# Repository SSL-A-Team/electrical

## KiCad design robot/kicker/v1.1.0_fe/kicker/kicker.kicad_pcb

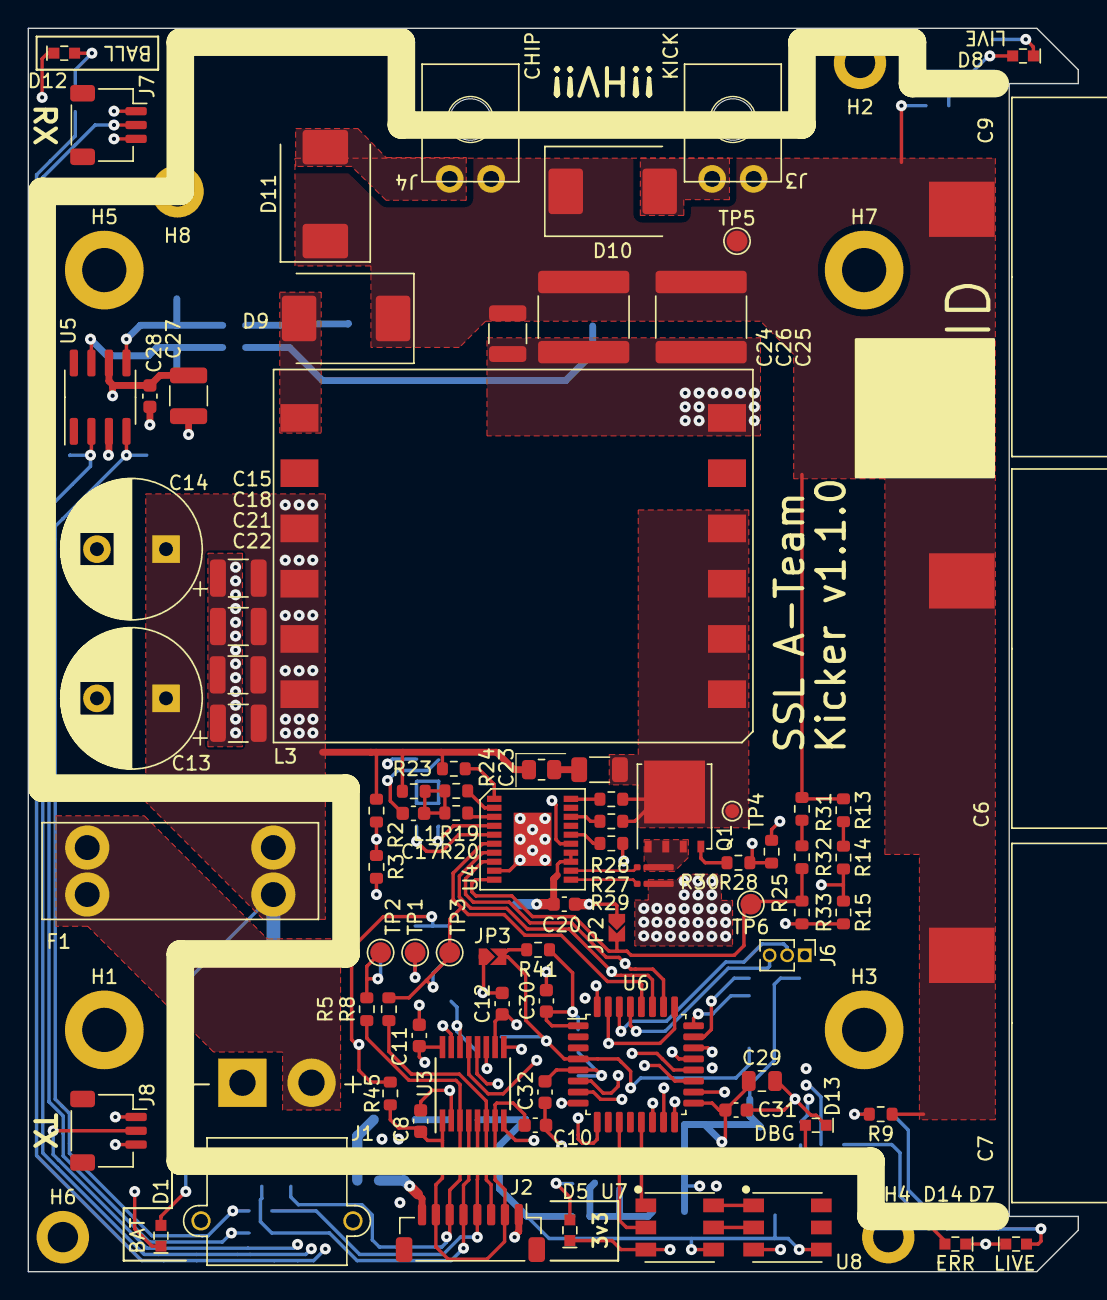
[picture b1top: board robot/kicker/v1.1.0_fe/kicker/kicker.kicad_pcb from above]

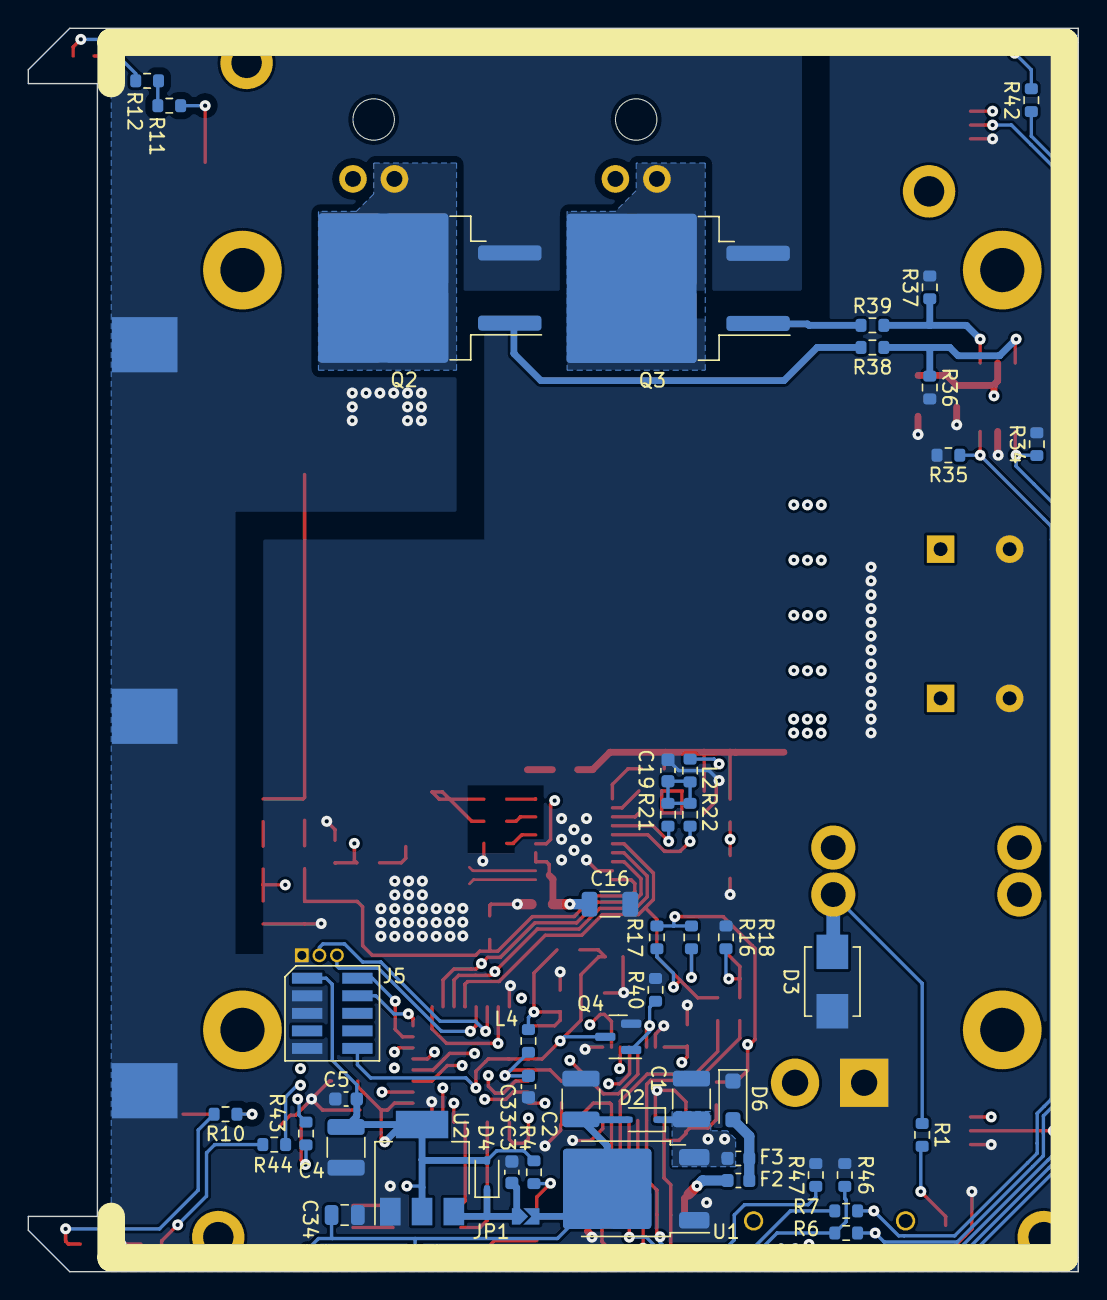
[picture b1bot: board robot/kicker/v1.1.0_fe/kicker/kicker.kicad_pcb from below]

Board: 4 copper layers, 76.0 x 90.0 mm, 139 parts (48 on the bottom side), 77 nets.

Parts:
C1: 22u 25V; C_1210_3225Metric
C2, C4: 47u 10V; C_1210_3225Metric
C3, C5, C33: 1u 10V; C_0603_1608Metric
C6, C7, C9: 1000uF 200V; ESMQ201VSN102MQ35S
C8, C10, C11, C12, C17, C19, C20, C28, C30, C31: 0.1u; C_0603_1608Metric
C13, C14: 220u 50V; CP_Radial_D10.0mm_P5.00mm
C15, C18, C21, C22: 10u 50V; C_1210_3225Metric
C16: 10u 35V; C_1206_3216Metric
C23: 0.1u 200V; C_1206_3216Metric
C24: 0.1u 500V; C_1210_3225Metric
C25, C26: 0.47u 500V; C_2225_5664Metric
C27: 10u 50v; C_1210_3225Metric
C29, C34: 4u7 25V; C_0805_2012Metric
C32: 10n 10V; C_0603_1608Metric
D1, D5, D13: Green; LED0603
D2, D4: CUS10S30,H3F; D_SOD-323
D3: 824521261; D_SMB_Non-Polar
D6: SMF12CA; D_SOD-123F
D7, D8: RED; LED0603
D9, D10, D11: MURS460; D_SMC
D12: Blue; LED0603
D14: Yellow; LED0603
F1: 40A; 3557-2
F2, F3: 1.5A Fast Blow; Fuse_0603_1608Metric
H1, H3, H5, H7: M3; MountingHole_3.2mm_M3_ISO7380_Pad
H2, H4, H6, H8: M2; MountingHole_2.2mm_M2_ISO14580_Pad
J1: XT30PW-M; AMASS_XT30PW-M_1x02_P2.50mm_Horizontal
J2: 1054052108; JST_SH_BM08B-SRSS-TB_1x08-1MP_P1.00mm_Vertical
J3, J4: 2157601002
J5: Conn_ARM_JTAG_SWD_10; Samtec-2x5pin-0.5mm
J6: Conn_01x03_Female; PinHeader_1x03_P1.27mm_Vertical
J7, J8: Conn_01x03; JST_SH_SM03B-SRSS-TB_1x03-1MP_P1.00mm_Horizontal
JP1: Power Iso.; SolderJumper-2_2.0x1.2mm_Closed
JP2: CCM_EN; SolderJumper-2_2.0x1.2mm_Closed
JP3: Disable Micro; SolderJumper-2_2.0x1.2mm_Open
L1, L2, L4: 650 @100MHz; R_0603_1608Metric
L3: GA3460-BL; GA34XX-BL
Q1: BSC0402NSATMA1; TDSON-8-1
Q2, Q3: IXGA48N60A3; TO-263-2
Q4: BSS138K; SOT-23
R1: 22k; R_0603_1608Metric
R2: 267k; R_0603_1608Metric
R3: 18k7; R_0603_1608Metric
R4, R42, R43, R44: 10k; R_0603_1608Metric
R5, R6, R7, R8: DNP; R_0603_1608Metric
R9, R10, R11, R12, R13, R14: 1M47; R_0603_1608Metric
R15: 15k; R_0603_1608Metric
R16, R17, R18, R34, R35, R36, R37, R40, R41, R46, R47: 100k; R_0603_1608Metric
R19: 316k 1%; R_0603_1608Metric
R20: 523k 1%; R_0603_1608Metric
R21: 205k 1%; R_0603_1608Metric
R22: 226k 1%; R_0603_1608Metric
R23, R26: 36k5 1%; R_0603_1608Metric
R24: 1 1%; R_0805_2012Metric
R25: 100k 1%; R_0603_1608Metric
R27: 80k6 1%; R_0603_1608Metric
R28: 10 1%; R_0603_1608Metric
R29: 4k21; R_0603_1608Metric
R30: 3m00 1% 1W; 1206-CS
R31, R32: 237k 1%; R_0603_1608Metric
R33: 2k94 1%; R_0603_1608Metric
R38, R39: 10; R_0603_1608Metric
R45: 0; R_0603_1608Metric
TP1: ~{DONE}; TestPoint_Pad_D1.5mm
TP2: CHG_EN; TestPoint_Pad_D1.5mm
TP3: ~{FAULT}; TestPoint_Pad_D1.5mm
TP4: SPICE: V_{drain} <<<HIGH VOLTAGE>>>; TestPoint_Pad_D1.0mm
TP5: SPICE: V_{out} <<<HIGH VOLTAGE>>>; TestPoint_Pad_D1.5mm
TP6: FB; TestPoint_Pad_D1.5mm
U1: LM1117-5.0; TO-252-2
U2: LM1117-3.3; SOT-223-3_TabPin2
U3: ADUM7441; QSOP-16_3.9x4.9mm_P0.635mm
U4: LT3751; LT3751-FE
U5: IX4427; SOIC-8_3.9x4.9mm_P1.27mm
U6: STM32F030K6Tx; LQFP-32_7x7mm_P0.8mm
U7, U8: SK9822

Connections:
+3V3: C4.1, C5.1, C11.1, C12.1, C29.1, C30.1, C31.1, D4.2 (A), J5.1 (VTref), J7.1, J8.1, L4.1, R4.1, R16.1, R17.1, R41.1, R45.2, U2.2 (VO), U3.10 (V_{DD2B}), U3.16 (V_{DD2A}), U6.1 (VDD), U6.17 (VDD)
+5V: C2.1, C34.2, D2.2 (A), JP1.2 (B), U1.2 (VO), U7.4 (VCC), U8.4 (VCC)
+12V: C1.1, C16.1, C20.1, C27.1, C28.1, D2.1 (K), F3.2, L2.1, U1.3 (VI), U4.13 (V_{cc}), U4.14 (LVGATE), U5.6 (V+)
+BATT: C13.1, C14.1, C15.1, C18.1, C21.1, C22.1, D3.2 (A2), F1.2, L1.1, L3.9, L3.10, L3.11, L3.12, R1.1, R2.1, R23.2, R24.1
+V_{BATT(RAW)}: F1.1, J1.2
/12V0_UNPROT: F2.1, J2.8
/BOOT0: U3.13 (V_{OB}), U6.25 (PA15), U6.31 (BOOT0)
/BOOT0_KICK_PROT: J2.5, R6.1, R46.1, U3.4 (V_{IB})
/CMD_{CHG}: R5.2, R18.1, TP2.1, U4.8 (CHARGE), U6.26 (PB3)
/CMD_{chip}: R7.2, R35.1, U5.4 (INB), U6.15 (PB1)
/CMD_{kick}: R6.2, R34.1, U5.2 (INA), U6.14 (PB0)
/DL1S: R9.2, R10.1
/DL2S: R11.2, R12.1
/HVMS: R13.2, R14.1
/HV_MON: R14.2, R15.1, U6.6 (PA0)
/RST: Q4.1 (G), R40.1, U3.14 (V_{OA})
/RST_CHG_PROT: J2.6, R5.1, R47.1, U3.3 (V_{IA})
/RX: U3.12 (V_{OC}), U6.20 (PA10)
/RX_CHIP_PROT: J2.4, R7.1, U3.5 (V_{IC})
/STATUS_{~DONE}: R16.2, TP1.1, U4.7 (~DONE), U6.27 (PB4)
/STATUS_{~FAULT}: R8.2, R17.2, TP3.1, U4.6 (~FAULT), U6.28 (PB5)
/TX: U3.11 (V_{ID}), U6.19 (PA9)
/TX_FAULT_PROT: J2.3, R8.1, U3.6 (V_{OD})
/V_{batt}_MON: R2.2, R3.1, U6.7 (PA1)
/digital/BALL_RX: J8.2, U6.9 (PA3)
/digital/BALL_TX: J7.2, U6.8 (PA2)
/digital/DOTSTAR_MOSI: U6.13 (PA7), U7.1 (SDI)
/digital/DOTSTAR_SCK: U6.11 (PA5), U7.2 (CKI)
/digital/LED_BLUE: R42.1, U6.18 (PA8)
/digital/LED_GREEN: R43.1, U6.21 (PA11)
/digital/LED_RED: R44.1, U6.22 (PA12)
/digital/NRST: J5.10 (~RESET), JP3.2 (B), Q4.3 (D), R41.2, U6.4 (NRST)
/digital/SWDCLK: J5.4 (SWDCLK/TCK), U6.24 (PA14)
/digital/SWDIO: J5.2 (SWDIO/TMS), U6.23 (PA13)
/digital/VDDA: C32.1, C33.1, L4.2, U6.5 (VDDA)
/flyback_charger/CSN: R30.2, U4.11 (CSN)
/flyback_charger/CSP: R30.3, U4.12 (CSP)
/flyback_charger/FB: JP2.2 (B), R32.1, R33.2, TP6.1, U4.10 (FB)
/flyback_charger/HVFBS: R31.1, R32.2
/flyback_charger/HVGATE: R25.2, R28.1, U4.15 (HVGATE)
/flyback_charger/HV_AC: D9.2 (A), L3.7
/flyback_charger/OVLO1: R20.2, U4.3 (OVLO1)
/flyback_charger/OVLO2: R22.2, U4.5 (OVLO2)
/flyback_charger/RBG: R29.1, U4.16 (RBG)
/flyback_charger/RDCM: R26.1, U4.20 (RDCM)
/flyback_charger/RV_{out}: R27.1, U4.18 (RV_{OUT})
/flyback_charger/RV_{trans}: R23.1, U4.1 (RV_{TRANS})
/flyback_charger/UVLO1: R19.2, U4.2 (UVLO1)
/flyback_charger/UVLO2: R21.2, U4.4 (UVLO2)
/flyback_charger/V_{batt}_FILT: C17.1, L1.2, R19.1, R20.1
/flyback_charger/V_{cc}_FILT: C19.1, L2.2, R21.1, R22.1
/flyback_charger/V_{solenoid}: C6.1, C7.1, C9.1, C24.1, C25.1, C26.1, D9.1 (K), D10.1 (K), D11.1 (K), J3.2, J4.2, R9.1, R11.1, R13.1, R31.2, TP5.1
/flyback_charger/V_{trans}: C23.2, L3.1, L3.2, L3.3, L3.4, Q1.5 (D), R26.2, R27.2, TP4.1
/flyback_charger/V_{trans}_SOURCE: Q1.1 (S), Q1.2 (S), Q1.3 (S), R30.4
/solenoid_control/CHIP_SW: D11.2 (A), J4.1, Q3.2 (C)
/solenoid_control/GATE_{chip}: R37.1, R39.1, U5.5 (OUTB)
/solenoid_control/GATE_{chip}_FILT: Q3.1 (G), R39.2
/solenoid_control/GATE_{kick}: R36.1, R38.1, U5.7 (OUTA)
/solenoid_control/GATE_{kick}_FILT: Q2.1 (G), R38.2
/solenoid_control/KICK_SW: D10.2 (A), J3.1, Q2.2 (C)
GND: C1.2, C2.2, C3.2, C4.2, C5.2, C6.2, C7.2, C8.2, C9.2, C10.2, C11.2, C12.2, C13.2, C14.2, C15.2, C16.2, C17.2, C18.2, C19.2, C20.2, C21.2, C22.2, C24.2, C25.2, C26.2, C27.2, C28.2, C29.2, C30.2, C31.2, C32.2, C33.2, C34.1, D1.1 (K), D3.1 (A1), D5.1 (K), D6.1 (A1), D7.1 (K), D8.1 (K), D12.1 (K), D13.1 (K), D14.1 (K), J1.1, J2.1, J5.3 (GND), J5.5 (GND), J5.9 (GNDDetect), J6.1, J7.3, J8.3, JP2.1 (A), JP3.1 (A), L3.6, Q2.3 (E), Q3.3 (E), Q4.2 (S), R3.2, R15.2, R18.2, R25.1, R29.2, R30.1, R33.1, R34.2, R35.2, R36.2, R37.2, R40.2, R46.2, R47.2, U1.1 (GND), U2.1 (GND), U3.2 (GND_{1}), U3.8 (GND_{1}), U3.9 (GND_{2}), U3.15 (GND_{2}), U4.9 (CLAMP), U4.21 (GND), U5.3 (GND), U6.16 (VSS), U6.32 (VSS), U7.3 (GND), U8.3 (GND)
unnamed: C3.1, D4.1 (K), JP1.1 (A), U2.3 (VI)
unnamed: C23.1, R24.2
unnamed: D1.2 (A), R1.2
unnamed: D5.2 (A), R4.2
unnamed: D6.2 (A2), F2.2, F3.1
unnamed: D7.2 (A), R10.2
unnamed: D8.2 (A), R12.2
unnamed: D12.2 (A), R42.2
unnamed: D13.2 (A), R43.2
unnamed: D14.2 (A), R44.2
unnamed: J6.2, U6.30 (PB7)
unnamed: J6.3, U6.29 (PB6)
unnamed: Q1.4 (G), R28.2
unnamed: U7.5 (CKO), U8.2 (CKI)
unnamed: U7.6 (SDO), U8.1 (SDI)
VBUS: C8.1, C10.1, J2.2, J2.7, R45.1, U3.1 (V_{DD1A}), U3.7 (V_{DD1B})

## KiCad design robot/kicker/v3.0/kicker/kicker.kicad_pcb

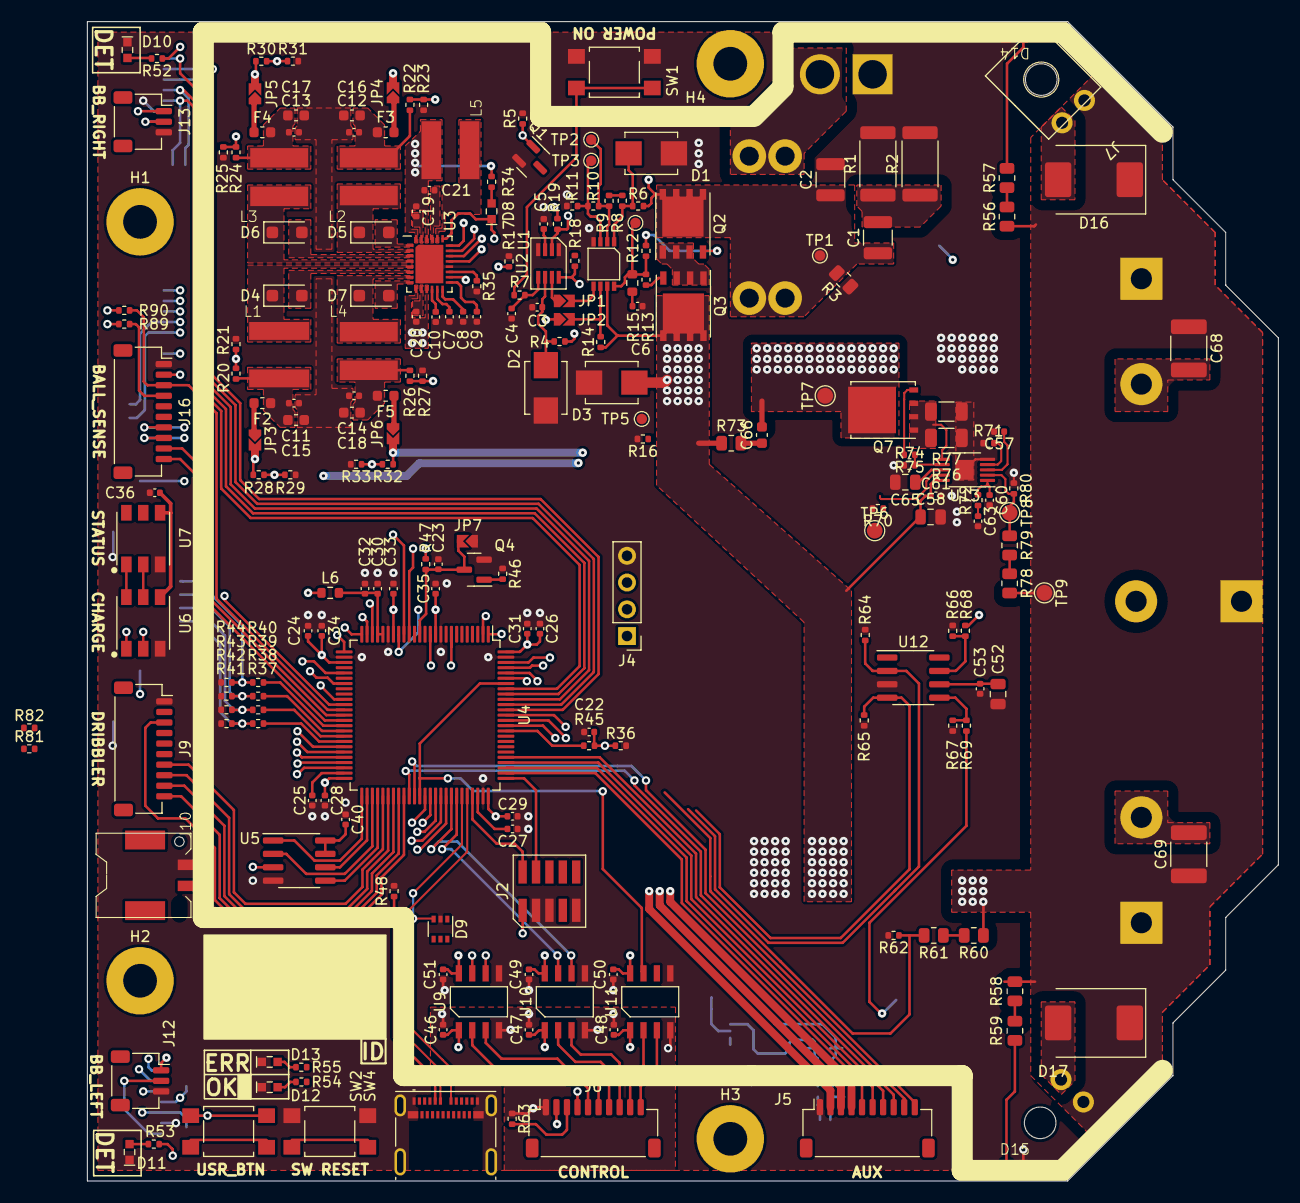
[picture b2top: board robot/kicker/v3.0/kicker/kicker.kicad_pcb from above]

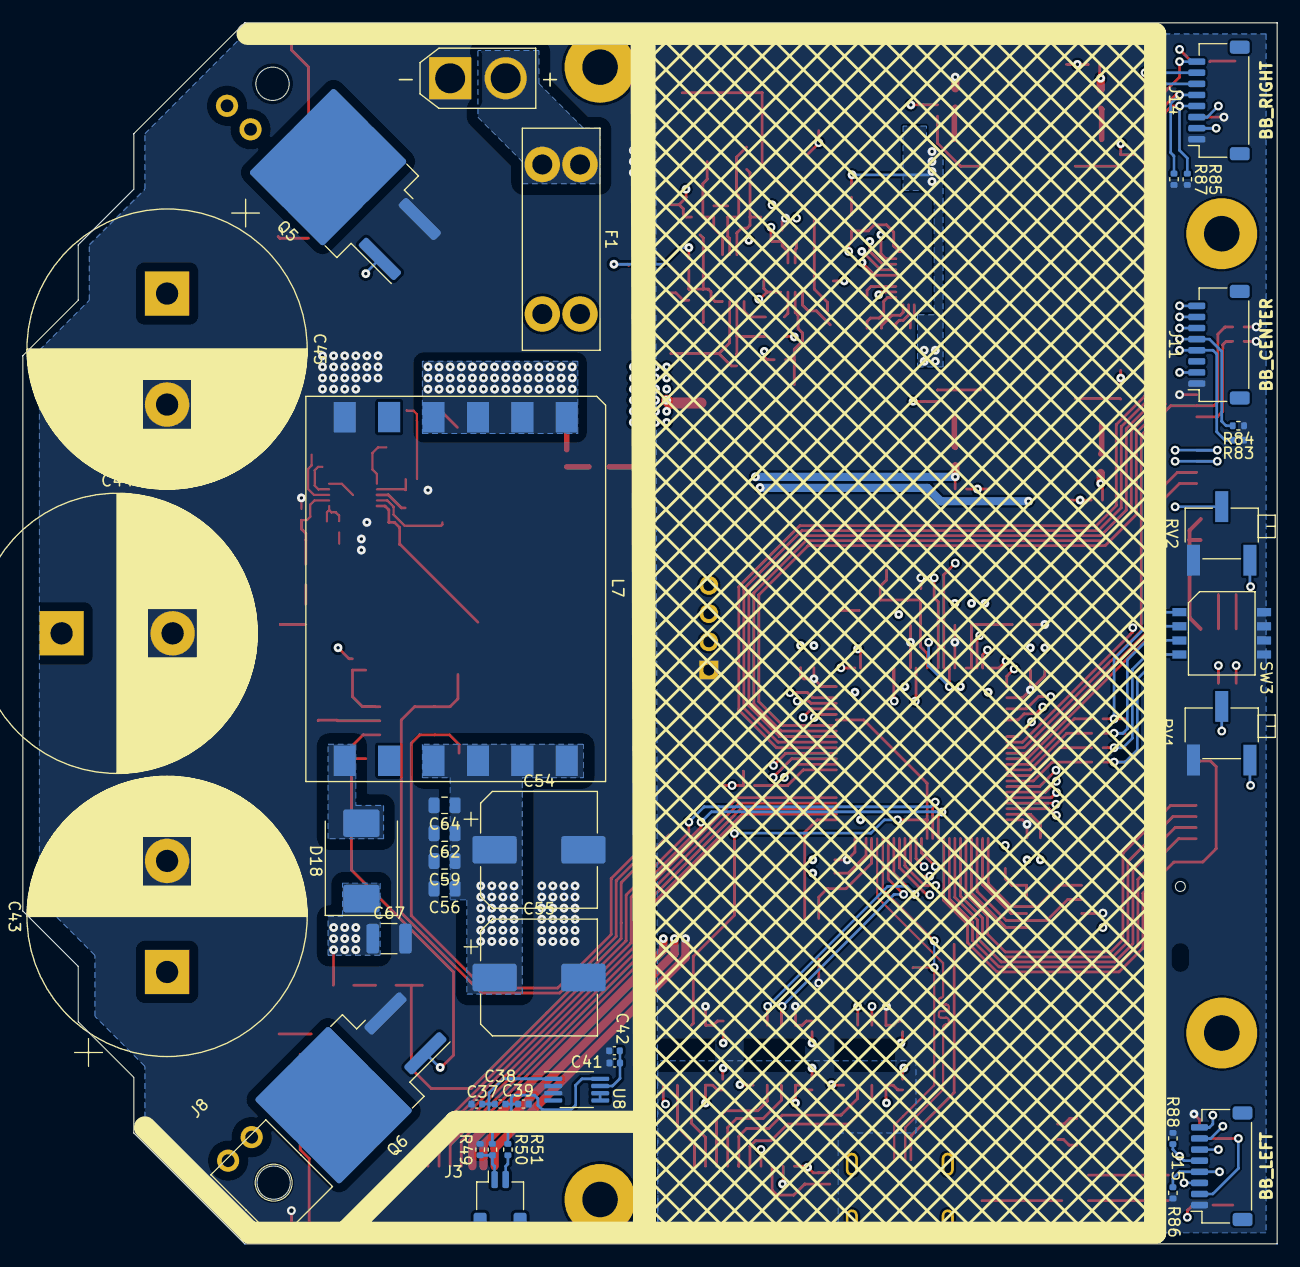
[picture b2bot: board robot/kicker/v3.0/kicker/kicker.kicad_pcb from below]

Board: 4 copper layers, 113.0 x 110.0 mm, 252 parts (39 on the bottom side), 184 nets.

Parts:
C1: 10u 100V; C_1210_3225Metric
C2: 10u 63V; C_1210_3225Metric
C3, C4, C5, C22, C23, C28, C29, C30, C31, C33, C34, C35, C38, C40, C41, C46, C47, C48, C49, C50, C51, C53, C60, C61: 100n 50V; C_0402_1005Metric
C6: 4.7n 63V; C_0402_1005Metric
C7, C8, C37, C39: 10n 6.3V; C_0402_1005Metric
C9, C10: 470n 6.3V; C_0402_1005Metric
C11, C12, C13, C14, C19, C20, C21, C32: 1u 50V; C_0402_1005Metric
C15, C16, C17, C18: 10u 25V; C_0603_1608Metric
C24, C25, C26, C27, C36: 4.7u 6.3V; C_0402_1005Metric
C42: 10u 6.3V; C_0402_1005Metric
C43, C44, C45: 1000uF 200V; CP_Radial_D25.0mm_P10.00mm_SnapIn
C52, C56, C58, C59, C62, C64: 10u 50V; C_0805_2012Metric
C54, C55: 220u 50V; CP_Elec_10x10
C57: 10n 50V; C_0402_1005Metric
C63: 6.8n 50V; C_0402_1005Metric
C65: 4.7u 50V; C_0805_2012Metric
C66: 100n 200V; C_0603_1608Metric
C67: 100n 500V; C_1210_3225Metric
C68, C69: 470n 500V; C_1812_4532Metric
D1, D2, D3: 824521261; D_SMB_Non-Polar
D4, D5, D6, D7: DSS14U; D_SOD-123F
D8, D13: Red; LED0603
D9: PESD3V3L5UY; SOT-363_SC-70-6
D10, D11: Blue; LED0603
D12: Green; LED0603
D14, D15: Red; APA1606
D16, D17: MURS460; D_SMC
D18: HS5M; D_SMC
F1: 15A; 3557-2
F2, F3, F4, F5: 1.0A; Fuse_0603_1608Metric
H1, H2, H3, H4: M3; MountingHole_3.2mm_M3_Pad
J1: XT30-F; AMASS_XT30U-M_1x02_P5.0mm_Vertical
J2: Conn_ARM_JTAG_SWD_10; Samtec-2x5pin-0.5mm
J3: Conn_01x02; JST_SH_SM02B-SRSS-TB_1x02-1MP_P1.00mm_Horizontal
J4: Conn_01x04_Pin; PinHeader_1x04_P2.54mm_Vertical
J5, J6, J9, J16: Conn_01x10; JST_SH_SM10B-SRSS-TB_1x10-1MP_P1.00mm_Horizontal
J7, J8: Conn_01x02; 2157601002
J10: Conn_01x02; SM02B-PASS-TBT
J11, J14, J15: Conn_01x08; JST_SH_SM08B-SRSS-TB_1x08-1MP_P1.00mm_Horizontal
J12, J13: Conn_01x03; JST_SH_SM03B-SRSS-TB_1x03-1MP_P1.00mm_Horizontal
JP1: BTN_EN; SolderJumper-2_2.0x1.2mm_Closed
JP2: PWR_EN; SolderJumper-2_2.0x1.2mm_Closed
JP3: 12v0 EN; SolderJumper-2_2.0x1.2mm_Open
JP4: 3v3 EN; SolderJumper-2_2.0x1.2mm_Open
JP5: 5v0 EN; SolderJumper-2_2.0x1.2mm_Open
JP6: 6v2 EN; SolderJumper-2_2.0x1.2mm_Open
JP7: Disable Micro; SolderJumper-2_2.0x1.2mm_Open
L1: ASPI-6045S-220M-T; ASPI-6045S
L2, L3, L4, L5: SDCHA1V5040-150-R; SDCHA1V50
L6: 650 @100MHz; R_0603_1608Metric
L7: GA3460-BL; GA34XX-BL
P1: USB_C_Plug_USB2.0; USB_C_Receptacle_Molex_105450-0101
Q1: BSS138; SOT-23
Q2, Q3: SQJA80EP-T1_GE3; PowerPAK_SO-8L_Single
Q4: BSS138K; SOT-23
Q5, Q6: IXGA48N60A3; TO-263-2
Q7: BSC0402NSATMA1; TDSON-8-1
R1, R2: 1; R_2512_6332Metric
R3, R56, R57, R58, R59: 1.47M; R_0805_2012Metric
R4, R6, R7, R70: 1k; R_0402_1005Metric
R5, R14, R18, R19, R36, R41, R42, R43, R44, R47, R50, R51, R52, R53, R54, R55, R64, R65, R81, R82, R89, R90: 10k; R_0402_1005Metric
R8: 510k; R_0402_1005Metric
R9: 430k; R_0402_1005Metric
R10: 14.7k; R_0402_1005Metric
R11: 15.4k; R_0402_1005Metric
R12, R13, R68, R69, R75: 10; R_0402_1005Metric
R15: 5.1k; R_0603_1608Metric
R16, R17, R46, R66, R67, R74: 100k; R_0402_1005Metric
R20, R71: 140k 1%; R_0402_1005Metric
R21, R23, R25, R27, R29, R31, R33: 10k 1%; R_0402_1005Metric
R22: 31.6k 1%; R_0402_1005Metric
R24: 53.6k 1%; R_0402_1005Metric
R26: 68.1k 1%; R_0402_1005Metric
R28: 110k 1%; R_0402_1005Metric
R30: 40.2k 1%; R_0402_1005Metric
R32: 52.3k 1%; R_0402_1005Metric
R34: 2.2k; R_0402_1005Metric
R35: 10.7k 1%; R_0402_1005Metric
R37, R38, R39, R40, R45, R63: 330; R_0402_1005Metric
R48: 5.1k; R_0402_1005Metric
R49: 1M; R_0402_1005Metric
R60, R61: 475k; R_0805_2012Metric
R62: 4.75k; R_0402_1005Metric
R72: 22k 1%; R_0402_1005Metric
R73: 1; R_0805_2012Metric
R76, R77: 4m 1%; R_1206_3216Metric
R78, R79: 976k 0.1%; R_0805_2012Metric
R80: 17.4k 0.1%; R_0402_1005Metric
R83, R84, R85, R86, R87, R88: 2.1k; R_0402_1005Metric
RV1: ACFG1; Potentiometer_Bourns_3269X_Horizontal
RV2: ACFG2; Potentiometer_Bourns_3269X_Horizontal
SW1: PWR_ON; SW_SPST_TL3305A
SW2: BTN0; SW_SPST_TL3305A
SW3: SW_DIP_x04; CHP-041TB
SW4: RST; SW_SPST_TL3305A
TP1: VBatt EOS; TestPoint_Pad_D1.0mm
TP2: LTC4367 UV EOS; TestPoint_Pad_D1.0mm
TP3: LTC4367 OV EOS; TestPoint_Pad_D1.0mm
TP4: Gate SS; TestPoint_Pad_D1.0mm
TP5: VBatt Sys; TestPoint_Pad_D1.0mm
TP6: CHG_EN; TestPoint_Pad_D1.5mm
TP7: SPICE: V_{drain} <<<HIGH VOLTAGE>>>; TestPoint_Pad_D1.5mm
TP8: FB; TestPoint_Pad_D1.5mm
TP9: SPICE: V_{out} <<<HIGH VOLTAGE>>>; TestPoint_Pad_D1.5mm
U1: LTC4367; MS8
U2: LTC2955-1; LTC2955-TS8
U3: LT3504; UFD
U4: STM32F407VETx; LQFP-100_14x14mm_P0.5mm
U5: AT25DF041x-UxN-x; SOIC-8_3.9x4.9mm_P1.27mm
U6, U7: SK9822
U8: AD8494; MSOP-8_3x3mm_P0.65mm
U9, U11: ISO6720-Q1; ISO672X
U10: ISO6721-Q1; ISO672X
U12: IX4427; SOIC-8_3.9x4.9mm_P1.27mm
U13: LT3757EMSE; MSOP-10-1EP_3x3mm_P0.5mm_EP1.68x1.88mm

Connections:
+3V3: C24.2, C26.2, C28.1, C29.1, C31.1, C33.1, C34.1, C35.1, C40.2, C41.1, C42.2, C49.1, C50.1, C51.1, J2.1 (VTref), J4.1, J5.2, J9.2, J11.1, J12.1, J13.1, J14.1, J15.1, J16.2, JP4.2 (B), L6.1, R18.1, R19.1, R47.1, R81.1, R82.1, R83.1, R84.1, R85.1, R86.1, R87.1, R88.1, R89.1, R90.1, RV1.1, RV2.1, SW2.2, SW3.5, SW3.6, SW3.7, SW3.8, U4.6 (VBAT), U4.11 (VDD), U4.19 (VDD), U4.28 (VDD), U4.50 (VDD), U4.75 (VDD), U4.100 (VDD), U5.3 (~WP/IO2), U5.7 (~HOLD/IO3), U5.8 (VCC), U8.7 (+Vs), U9.8 (VCC2), U10.8 (VCC2), U11.8 (VCC2)
+5V: C36.2, J5.3, JP5.2 (B), R30.1, U6.4 (VCC), U7.4 (VCC)
+6V: J5.4, JP6.2 (B), R32.1
+12V: C52.1, C53.1, C65.1, JP3.2 (B), R28.1, U12.6 (V+), U13.8 (INTVCC)
+BATT: C19.1, C20.1, C21.2, C54.1, C55.1, C56.1, C58.1, C59.1, C61.1, C62.1, C64.1, D3.2 (A2), J10.1, L5.2, L7.9, L7.10, L7.11, L7.12, Q3.5 (D), R14.1, R16.1, R34.1, R73.1, TP5.1, U1.7 (V_{OUT}), U3.9 (V_{IN}), U3.11 (V_{IN}), U3.26 (V_{IN}), U3.28 (V_{IN}), U13.10 (VIN)
/Ball Sense/8MHZ_CLK_REF: J9.5, J16.5, U4.12 (PH0), U9.7 (OUTA)
/Ball Sense/32KHZ_CLK_REF: J9.6, J16.6, U4.8 (PC14), U9.6 (OUTB)
/Ball Sense/SENSE_BOOT_UART.BOOT0: J16.9, U4.38 (PE7)
/Ball Sense/SENSE_BOOT_UART.RST: J16.10, U4.39 (PE8)
/Ball Sense/SENSE_BOOT_UART.RX: J16.8, U4.26 (PA3)
/Ball Sense/SENSE_BOOT_UART.TX: J16.7, U4.25 (PA2)
/Ball Sense/SENSE_BOOT_UART.~DET: J16.3, R90.2, U4.37 (PB2)
/Breakbeam/BB_CENTER.AGPIO: J11.2, U4.34 (PC5)
/Breakbeam/BB_CENTER.INT: J11.8, U4.46 (PE15)
/Breakbeam/BB_CENTER.RST: J11.6, U4.45 (PE14)
/Breakbeam/BB_CENTER.SCL: J11.5, R84.2, U4.47 (PB10)
/Breakbeam/BB_CENTER.SDA: J11.4, R83.2, U4.48 (PB11)
/Breakbeam/BB_CENTER.~DET: J11.7, U4.44 (PE13)
/Breakbeam/BB_LEFT.AGPIO: J12.2, J15.2, U4.24 (PA1)
/Breakbeam/BB_LEFT.INT: J15.8, U4.65 (PC8)
/Breakbeam/BB_LEFT.RST: J15.6, U4.64 (PC7)
/Breakbeam/BB_LEFT.SCL: J15.5, R88.2, U4.67 (PA8)
/Breakbeam/BB_LEFT.SDA: J15.4, R86.2, U4.66 (PC9)
/Breakbeam/BB_LEFT.~DET: J15.7, U4.63 (PC6)
/Breakbeam/BB_RIGHT.AGPIO: J13.2, J14.2, U4.23 (PA0)
/Breakbeam/BB_RIGHT.INT: J14.8, U4.91 (PB5)
/Breakbeam/BB_RIGHT.RST: J14.6, U4.90 (PB4)
/Breakbeam/BB_RIGHT.SCL: J14.5, R87.2, U4.92 (PB6)
/Breakbeam/BB_RIGHT.SDA: J14.4, R85.2, U4.93 (PB7)
/Breakbeam/BB_RIGHT.~DET: J14.7, U4.89 (PB3)
/Dribbler/DRIB_BOOT_UART.BOOT0: J9.9, U4.57 (PD10)
/Dribbler/DRIB_BOOT_UART.RST: J9.10, U4.58 (PD11)
/Dribbler/DRIB_BOOT_UART.RX: J9.8, U4.56 (PD9)
/Dribbler/DRIB_BOOT_UART.TX: J9.7, U4.55 (PD8)
/Dribbler/DRIB_BOOT_UART.~DET: J9.3, R82.2, U4.59 (PD12)
/Power Protection/PGOOD_{VBATT}: JP2.1 (A), R17.1, U3.16 (EN/UVLO)
/Power Protection/V_{BATT}: F1.1, J1.2
/Power Protection/V_{BATT}_FUSED: C1.1, C2.1, F1.2, Q2.5 (D), R3.2, R4.2, R6.2, TP1.1
/digital/AUX_GPIO1: J5.9, U4.60 (PD13)
/digital/AUX_GPIO2: J5.10, U4.61 (PD14)
/digital/AUX_MISO: J5.7, U4.79 (PC11)
/digital/AUX_MOSI: J5.8, U4.80 (PC12)
/digital/AUX_NSS: J5.5, U4.77 (PA15)
/digital/AUX_SCK: J5.6, U4.78 (PC10)
/digital/BB_LED1_BLUE: R52.1, U4.1 (PE2)
/digital/BB_LED2_BLUE: R53.1, U4.2 (PE3)
/digital/CMD_{CHG}: R70.1, TP6.1, U4.3 (PE4), U13.9 (~SHDN/UVLO)
/digital/CMD_{CHIP}: R65.1, U4.5 (PE6), U12.4 (INB)
/digital/CMD_{KICK}: R64.1, U4.4 (PE5), U12.2 (INA)
/digital/DBG_HDR1: J4.2, U4.95 (PB8)
/digital/DBG_HDR2: J4.3, U4.96 (PB9)
/digital/DIP0: R40.2, U4.40 (PE9)
/digital/DIP1: R39.2, U4.41 (PE10)
/digital/DIP2: R38.2, U4.42 (PE11)
/digital/DIP3: R37.2, U4.43 (PE12)
/digital/DOTSTAR_MOSI: U4.32 (PA7), U6.1 (SDI)
/digital/DOTSTAR_SCK: U4.30 (PA5), U6.2 (CKI)
/digital/FLASH_MISO: U4.53 (PB14), U5.2 (SO/IO1)
/digital/FLASH_MOSI: U4.54 (PB15), U5.5 (SI/IO0)
/digital/FLASH_NSS: U4.51 (PB12), U5.1 (~CS)
/digital/FLASH_SCK: U4.52 (PB13), U5.6 (SCK)
/digital/LED_GREEN: R54.1, U4.97 (PE0)
/digital/LED_RED: R55.1, U4.98 (PE1)
/digital/MCU_BOOT_UART.BOOT0: U4.62 (PD15), U4.94 (BOOT0), U11.7 (OUTA)
/digital/MCU_BOOT_UART.PWR_EN: J6.4, Q1.1 (G), R5.2
/digital/MCU_BOOT_UART.RST: Q4.1 (G), R46.1, U11.6 (OUTB)
/digital/MCU_BOOT_UART.RX: U4.69 (PA10), U10.7 (INA)
/digital/MCU_BOOT_UART.TX: U4.68 (PA9), U10.6 (OUTB)
/digital/MCU_BOOT_UART.~DET: J6.3, R63.2
/digital/NRST: C23.1, D9.6 (K5), J2.10 (~RESET), JP7.2 (B), Q4.3 (D), R47.2, SW4.2, U4.14 (NRST)
/digital/PGOOD: D8.1 (K), U3.23 (PG), U4.88 (PD7)
/digital/PWR_BTN_PRESSED_~INT: R18.2, U2.8 (~INT), U4.86 (PD5)
/digital/PWR_KILL: R19.2, U2.2 (~KILL), U4.87 (PD6)
/digital/SWCLK: J2.4 (SWDCLK/TCK), U4.76 (PA14)
/digital/SWDIO: J2.2 (SWDIO/TMS), U4.72 (PA13)
/digital/TEMP_PROBE: U4.33 (PC4), U8.5 (SENSE), U8.6
/digital/USB_OTG_FS_D_N: D9.3 (K2), P1.A7 (D-), U4.70 (PA11)
/digital/USB_OTG_FS_D_P: D9.4 (K3), P1.A6 (D+), U4.71 (PA12)
/digital/USER_ADJ1: RV1.2, U4.35 (PB0)
/digital/USER_ADJ2: RV2.2, U4.36 (PB1)
/digital/USR_BTN: D9.5 (K4), R45.1, U4.85 (PD4)
/digital/V_{sense}_5v0: R30.2, R31.1, U4.17 (PC2)
/digital/V_{sense}_6v2: R32.2, R33.1, U4.18 (PC3)
/digital/V_{sense}_12v0: R28.2, R29.1, U4.16 (PC1)
/digital/V_{sense}_HV: D9.1 (K1), R61.2, R62.1, U4.15 (PC0)
/hv_kicker/DL1S: R56.2, R57.1
/hv_kicker/DL2S: R58.2, R59.1
/hv_kicker/HVMS: R60.2, R61.1
/hv_kicker/flyback_charger/CSP: Q7.1 (S), Q7.2 (S), Q7.3 (S), R76.2, R77.2, U13.6 (SENSE)
/hv_kicker/flyback_charger/FB: R79.1, R80.2, TP8.1, U13.2 (FBX)
/hv_kicker/flyback_charger/HVFBS: R78.1, R79.2
/hv_kicker/flyback_charger/HVGATE: R74.2, R75.1, U13.7 (GATE)
/hv_kicker/flyback_charger/HV_AC: D18.2 (A), L7.7
/hv_kicker/flyback_charger/V_{solenoid}: C43.1, C44.1, C45.1, C67.1, C68.1, C69.1, D16.1 (K), D17.1 (K), D18.1 (K), J7.2, J8.2, R56.1, R58.1, R60.1, R78.2, TP9.1
/hv_kicker/flyback_charger/V_{trans}: C66.2, L7.1, L7.2, L7.3, L7.4, Q7.5 (D), TP7.1
/hv_kicker/solenoid_control/CHIP_SW: D17.2 (A), J8.1, Q6.2 (C)
/hv_kicker/solenoid_control/GATE_{chip}: R67.1, R69.1, U12.5 (OUTB)
/hv_kicker/solenoid_control/GATE_{chip}_FILT: Q6.1 (G), R69.2
/hv_kicker/solenoid_control/GATE_{kick}: R66.1, R68.1, U12.7 (OUTA)
/hv_kicker/solenoid_control/GATE_{kick}_FILT: Q5.1 (G), R68.2
/hv_kicker/solenoid_control/KICK_SW: D16.2 (A), J7.1, Q5.2 (C)
/isol/BOOT_UART_BOOT0_ISOL: J6.9, U11.2 (INA)
/isol/BOOT_UART_RST_ISOL: J6.10, U11.3 (INB)
/isol/BOOT_UART_RX_ISOL: J6.7, U10.2 (OUTA)
/isol/BOOT_UART_TX_ISOL: J6.8, U10.3 (INB)
/isol/CLK_8M_ISOL: J6.5, U9.2 (INA)
/isol/CLK_32K_ISOL: J6.6, U9.3 (INB)
/isol/GND_ISOL: C46.2, C47.2, C48.2, J6.1, R63.1, U9.4 (GND1), U10.4 (GND1), U11.4 (GND1)
/isol/V_{logic}_ISOL: C46.1, C47.1, C48.1, J6.2, U9.1 (VCC1), U10.1 (VCC1), U11.1 (VCC1)
GND: C2.2, C3.2, C4.2, C5.2, C6.2, C7.2, C8.2, C9.2, C10.2, C11.2, C12.2, C13.2, C14.2, C15.2, C16.2, C17.2, C18.2, C19.2, C20.2, C22.2, C23.2, C24.1, C25.1, C26.1, C27.1, C28.2, C29.2, C30.2, C31.2, C32.2, C33.2, C34.2, C35.2, C36.1, C37.1, C39.2, C40.1, C41.2, C42.1, C43.2, C44.2, C45.2, C49.2, C50.2, C51.2, C52.2, C53.2, C54.2, C55.2, C56.2, C57.2, C58.2, C59.2, C60.2, C61.2, C62.2, C63.2, C64.2, C65.2, C67.2, C68.2, C69.2, D1.1 (A1), D2.1 (A1), D3.1 (A1), D9.2 (A), D10.1 (K), D11.1 (K), D12.1 (K), D13.1 (K), D14.1 (K), D15.1 (K), J1.1, J2.3 (GND), J2.5 (GND), J2.9 (GNDDetect), J4.4, J5.1, J9.1, J10.2, J11.3, J12.3, J13.3, J14.3, J15.3, J16.1, JP7.1 (A), L7.6, P1.A1 (GND), P1.A12 (GND), P1.B1 (GND), P1.B12 (GND), P1.S1 (SHIELD), Q1.2 (S), Q4.2 (S), Q5.3 (E), Q6.3 (E), R1.2, R2.2, R3.1, R5.1, R11.1, R16.2, R17.2, R21.2, R23.2, R25.2, R27.2, R29.2, R31.2, R33.2, R35.2, R36.2, R41.1, R42.1, R43.1, R44.1, R46.2, R48.2, R49.1, R62.2, R64.2, R65.2, R66.2, R67.2, R70.2, R71.1, R74.1, R76.1, R77.1, R80.1, RV1.3, RV2.3, SW1.1, SW4.1, U1.4 (GND), U2.1 (ON), U2.4 (GND), U3.10 (GND), U3.18 (GND), U3.27 (GND), U3.29 (GND), U4.10 (VSS), U4.20 (VSSA), U4.27 (VSS), U4.74 (VSS), U4.99 (VSS), U5.4 (GND), U6.3 (GND), U7.3 (GND), U8.2 (REF), U8.3 (-Vs), U9.5 (GND2), U10.5 (GND2), U11.5 (GND2), U12.3 (GND), U13.5 (SYNC), U13.11 (GND)
unnamed: C1.2, R1.1, R2.1
unnamed: C6.1, R15.2
unnamed: C11.1, C15.1, F2.1, L1.2, R20.1
unnamed: C12.1, C16.1, F3.1, L2.2, R22.1
unnamed: C13.1, C17.1, F4.1, L3.2, R24.1
unnamed: C14.1, C18.1, F5.1, L4.2, R26.1
unnamed: C22.1, R36.1, R45.2, SW2.1
unnamed: C63.1, R72.1
unnamed: C66.1, R73.2
unnamed: D1.2 (A2), R6.1, R8.1, U1.1 (V_{IN})
unnamed: C3.1, D2.2 (A2), R4.1, U2.6 (V_{in})
unnamed: D4.2 (A), U3.6 (DA1)
unnamed: D4.1 (K), L1.1, U3.5 (SW1)
unnamed: D5.2 (A), U3.1 (DA2)
unnamed: D5.1 (K), L2.1, U3.2 (SW2)
unnamed: D6.2 (A), U3.3 (DA3)
unnamed: D6.1 (K), L3.1, U3.4 (SW3)
unnamed: D7.2 (A), U3.8 (DA4)
unnamed: D7.1 (K), L4.1, U3.7 (SW4)
unnamed: D8.2 (A), R34.2
unnamed: D10.2 (A), R52.2
unnamed: D11.2 (A), R53.2
unnamed: D12.2 (A), R54.2
unnamed: D13.2 (A), R55.2
unnamed: D14.2 (A), R57.2
unnamed: D15.2 (A), R59.2
unnamed: J3.1, R49.2, R50.1
unnamed: J3.2, R51.1
unnamed: J9.4, R81.2
unnamed: J16.4, R89.2
unnamed: JP1.1 (A), U2.7 (EN)
unnamed: JP1.2 (B), U1.5 (~SHDN)
unnamed: JP2.2 (B), R14.2, U1.6 (~FAULT)
unnamed: F2.2, JP3.1 (A)
unnamed: F3.2, JP4.1 (A)
unnamed: F4.2, JP5.1 (A)
unnamed: F5.2, JP6.1 (A)
unnamed: P1.A5 (CC), R48.1
unnamed: Q1.3 (D), R7.2, SW1.2
unnamed: Q2.4 (G), R12.1
unnamed: Q2.1 (S), Q2.2 (S), Q2.3 (S), Q3.1 (S), Q3.2 (S), Q3.3 (S)
unnamed: Q3.4 (G), R13.2
unnamed: Q7.4 (G), R75.2
unnamed: R8.2, R9.1
unnamed: R37.1, R41.2, SW3.4
unnamed: R38.1, R42.2, SW3.3
unnamed: R39.1, R43.2, SW3.2
unnamed: R40.1, R44.2, SW3.1
unnamed: R12.2, R13.1, R15.1, TP4.1, U1.8 (GATE)
unnamed: R10.2, R11.2, TP3.1, U1.3 (OV)
unnamed: R9.2, R10.1, TP2.1, U1.2 (UV)
unnamed: C5.1, U2.3 (TMR)
unnamed: C4.1, R7.1, U2.5 (~PB)
unnamed: R35.1, U3.17 (RT/SYNC)
unnamed: C21.1, U3.25 (SKY)
unnamed: L5.1, U3.24 (SW5)
unnamed: R20.2, R21.1, U3.20 (FB1)
unnamed: C7.1, U3.13 (RUN/SS1)
unnamed: R22.2, R23.1, U3.22 (FB2)
unnamed: C8.1, U3.14 (RUN/SS2)
unnamed: R24.2, R25.1, U3.21 (FB3)
unnamed: C9.1, U3.15 (RUN/SS3)
unnamed: R26.2, R27.1, U3.19 (FB4)
unnamed: C10.1, U3.12 (RUN/SS4)
unnamed: C25.2, U4.49 (VCAP_1)
unnamed: C27.2, U4.73 (VCAP_2)
unnamed: C30.1, C32.1, L6.2, U4.21 (VREF+), U4.22 (VDDA)
unnamed: U6.5 (CKO), U7.2 (CKI)
unnamed: U6.6 (SDO), U7.1 (SDI)
unnamed: C38.2, C39.1, R51.2, U8.8 (+IN)
unnamed: C37.2, C38.1, R50.2, U8.1 (-IN)
unnamed: R71.2, U13.4 (RT)
unnamed: C57.1, U13.3 (SS)
unnamed: C60.1, R72.2, U13.1 (VC)
